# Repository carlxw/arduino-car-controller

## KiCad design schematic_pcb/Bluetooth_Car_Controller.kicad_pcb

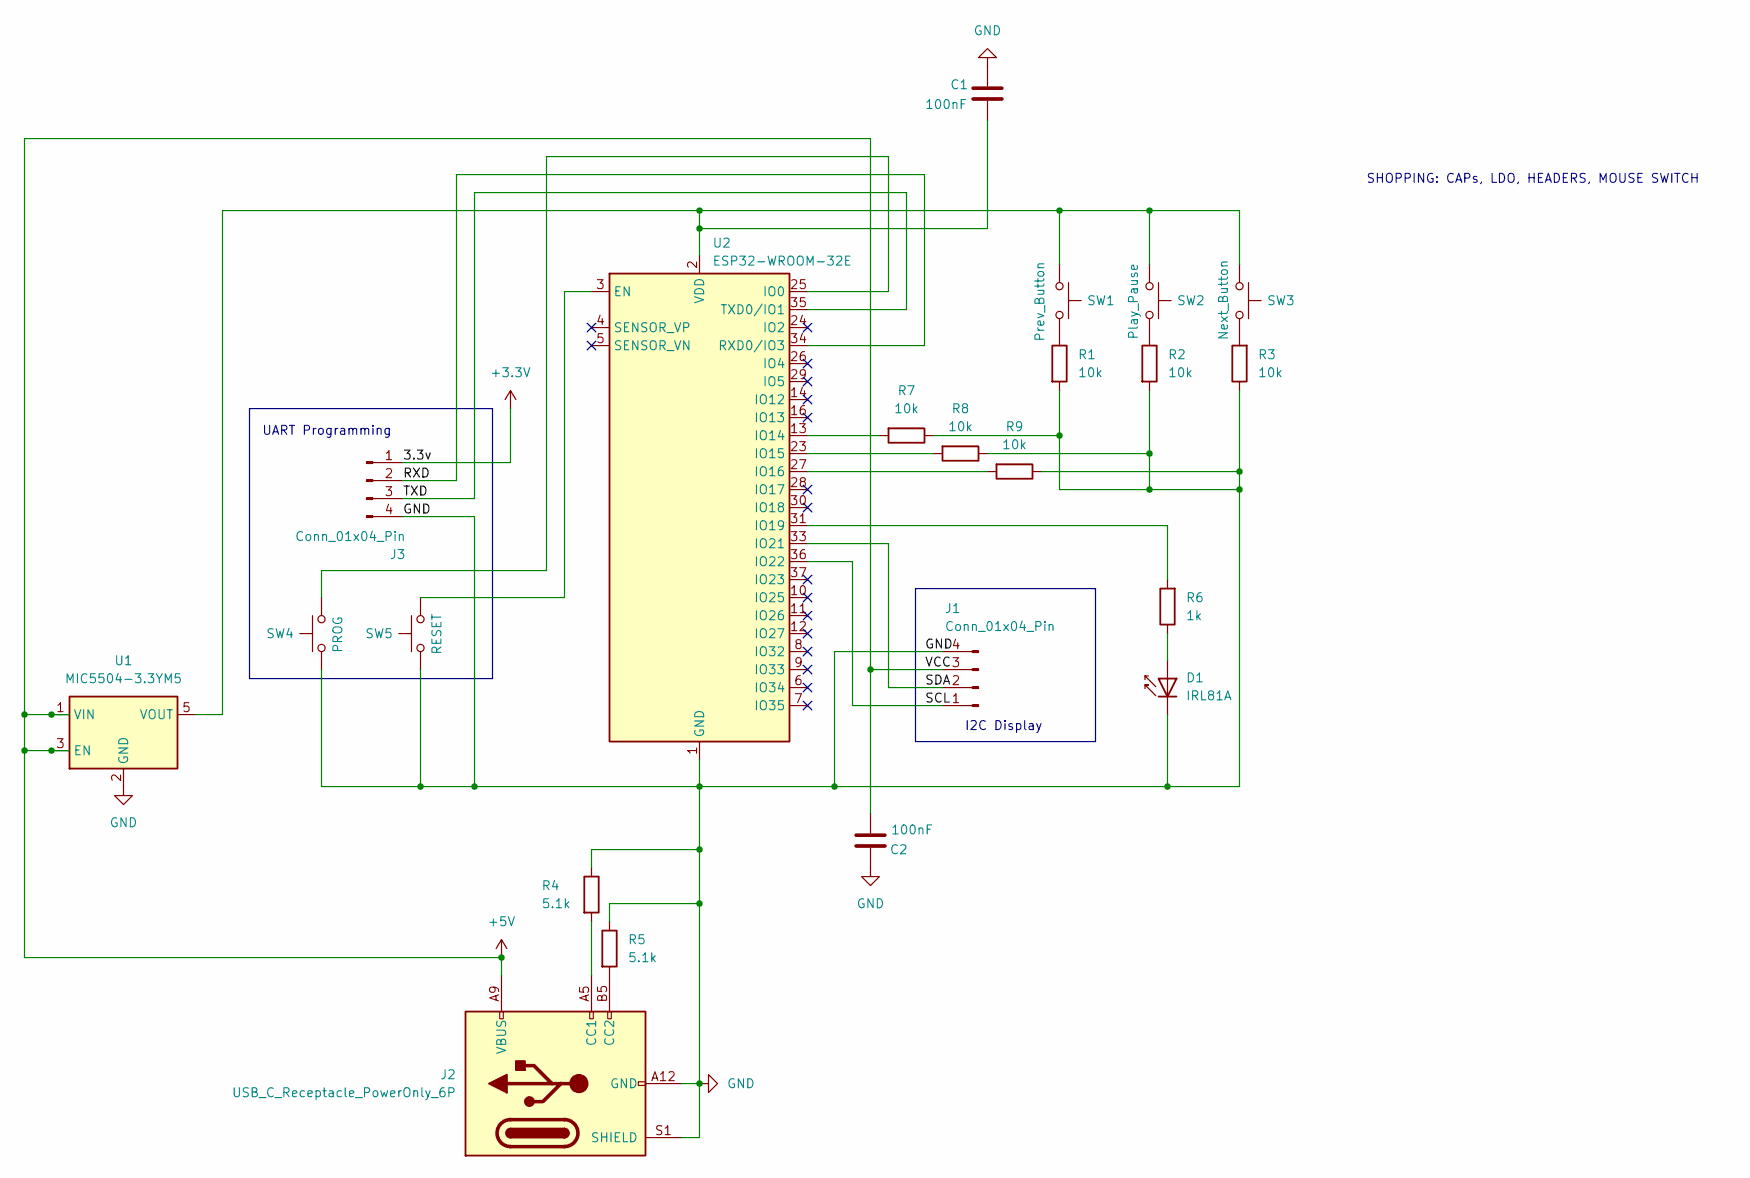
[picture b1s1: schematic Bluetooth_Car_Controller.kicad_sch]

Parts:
C1, C2: 100nF; C_0805_2012Metric_Pad1.18x1.45mm_HandSolder
D1: IRL81A; LED_SideEmitter_Rectangular_W4.5mm_H1.6mm
J1, J3: Conn_01x04_Pin; PinHeader_1x04_P2.54mm_Horizontal
J2: USB_C_Receptacle_PowerOnly_6P; USB_C_Receptacle_GCT_USB4125-xx-x-0190_6P_TopMnt_Horizontal
R1, R2, R3, R7, R8, R9: 10k; R_2512_6332Metric
R4, R5: 5.1k; R_2512_6332Metric
R6: 1k; R_2512_6332Metric
SW1: Prev_Button; SW_Cherry_MX_1.00u_PCB
SW2: Play_Pause; SW_Cherry_MX_1.00u_PCB
SW3: Next_Button; SW_Cherry_MX_1.00u_PCB
SW4: PROG; SW_PUSH_6mm_H5mm
SW5: RESET; SW_PUSH_6mm_H5mm
U1: MIC5504-3.3YM5; SOT-23-5
U2: ESP32-WROOM-32E; ESP32-WROOM-32D

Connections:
+5V: C2.2, J1.3, J2.A9 (VBUS), J2.B9 (VBUS), U1.1 (VIN), U1.3 (EN)
/RXD: J3.2, U2.34 (RXD0/IO3)
/SCL: J1.1, U2.36 (IO22)
/SDA: J1.2, U2.33 (IO21)
/TXD: J3.3, U2.35 (TXD0/IO1)
GND: C1.1, C2.1, D1.1 (K), J1.4, J2.A12 (GND), J2.B12 (GND), J2.S1 (SHIELD), J3.4, R1.2, R2.2, R3.1, R4.1, R5.1, R7.1, R8.1, R9.1, SW4.1, SW5.1, U1.2 (GND), U2.1 (GND), U2.15 (GND), U2.38 (GND), U2.39 (GND)
unnamed: D1.2 (A), R6.1
unnamed: J2.A5 (CC1), R4.2
unnamed: J2.B5 (CC2), R5.2
unnamed: R1.1, SW1.2
unnamed: R2.1, SW2.2
unnamed: R3.2, SW3.2
unnamed: SW5.2, U2.3 (EN)
unnamed: SW4.2, U2.25 (IO0)
unnamed: R7.2, U2.13 (IO14)
unnamed: R8.2, U2.23 (IO15)
unnamed: R9.2, U2.27 (IO16)
unnamed: R6.2, U2.31 (IO19)

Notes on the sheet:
SHOPPING: CAPs, LDO, HEADERS, MOUSE SWITCH
I2C Display
UART Programming

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
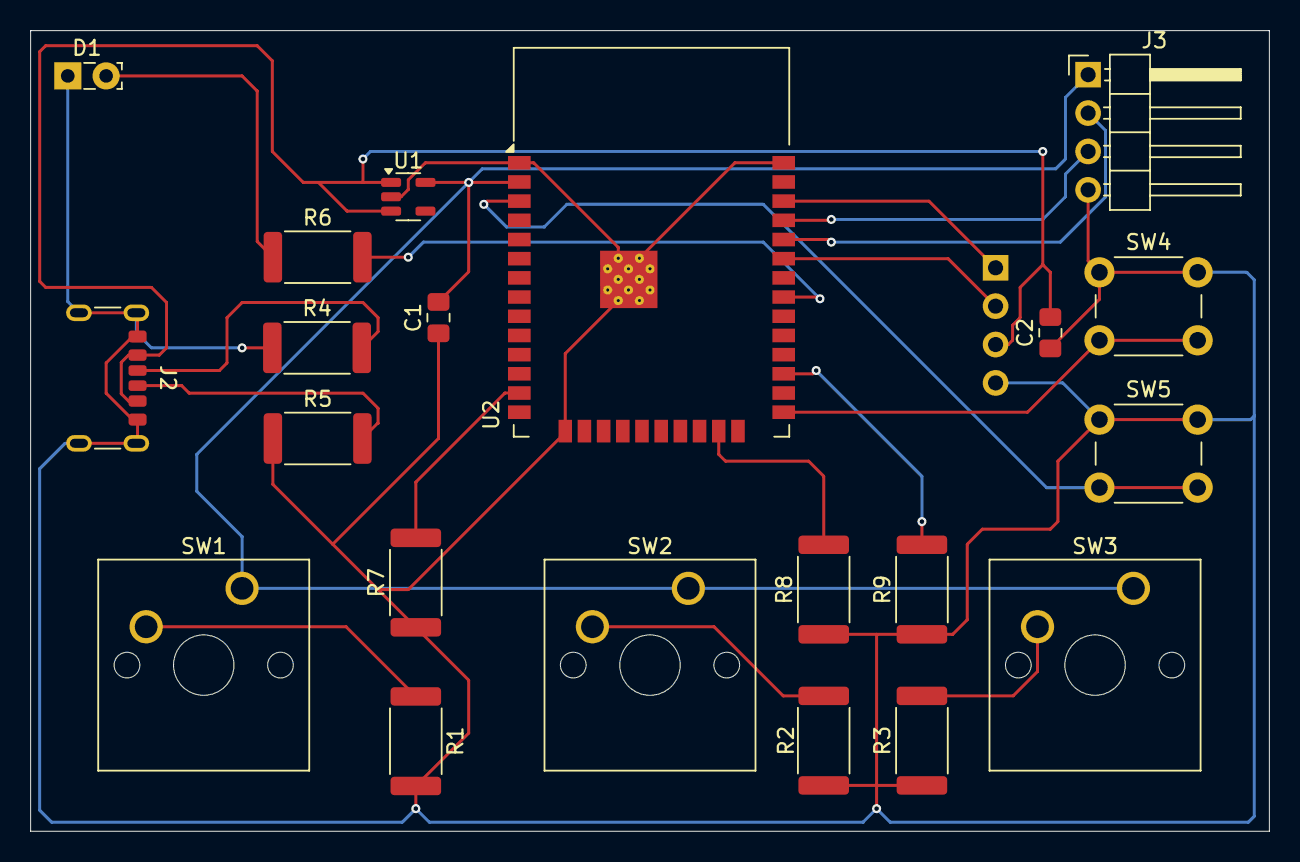
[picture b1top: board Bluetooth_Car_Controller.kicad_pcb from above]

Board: 2 copper layers, 82.0 x 53.0 mm, 22 parts (1 on the bottom side), 19 nets.

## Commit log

2025-01-12 Move all code to single main.cpp
2025-01-28 Finish one version of PCB
2025-02-16 Finish final code and schematic
2025-02-16 Finish schematic and final code
2025-02-27 Finalize code and schematic
